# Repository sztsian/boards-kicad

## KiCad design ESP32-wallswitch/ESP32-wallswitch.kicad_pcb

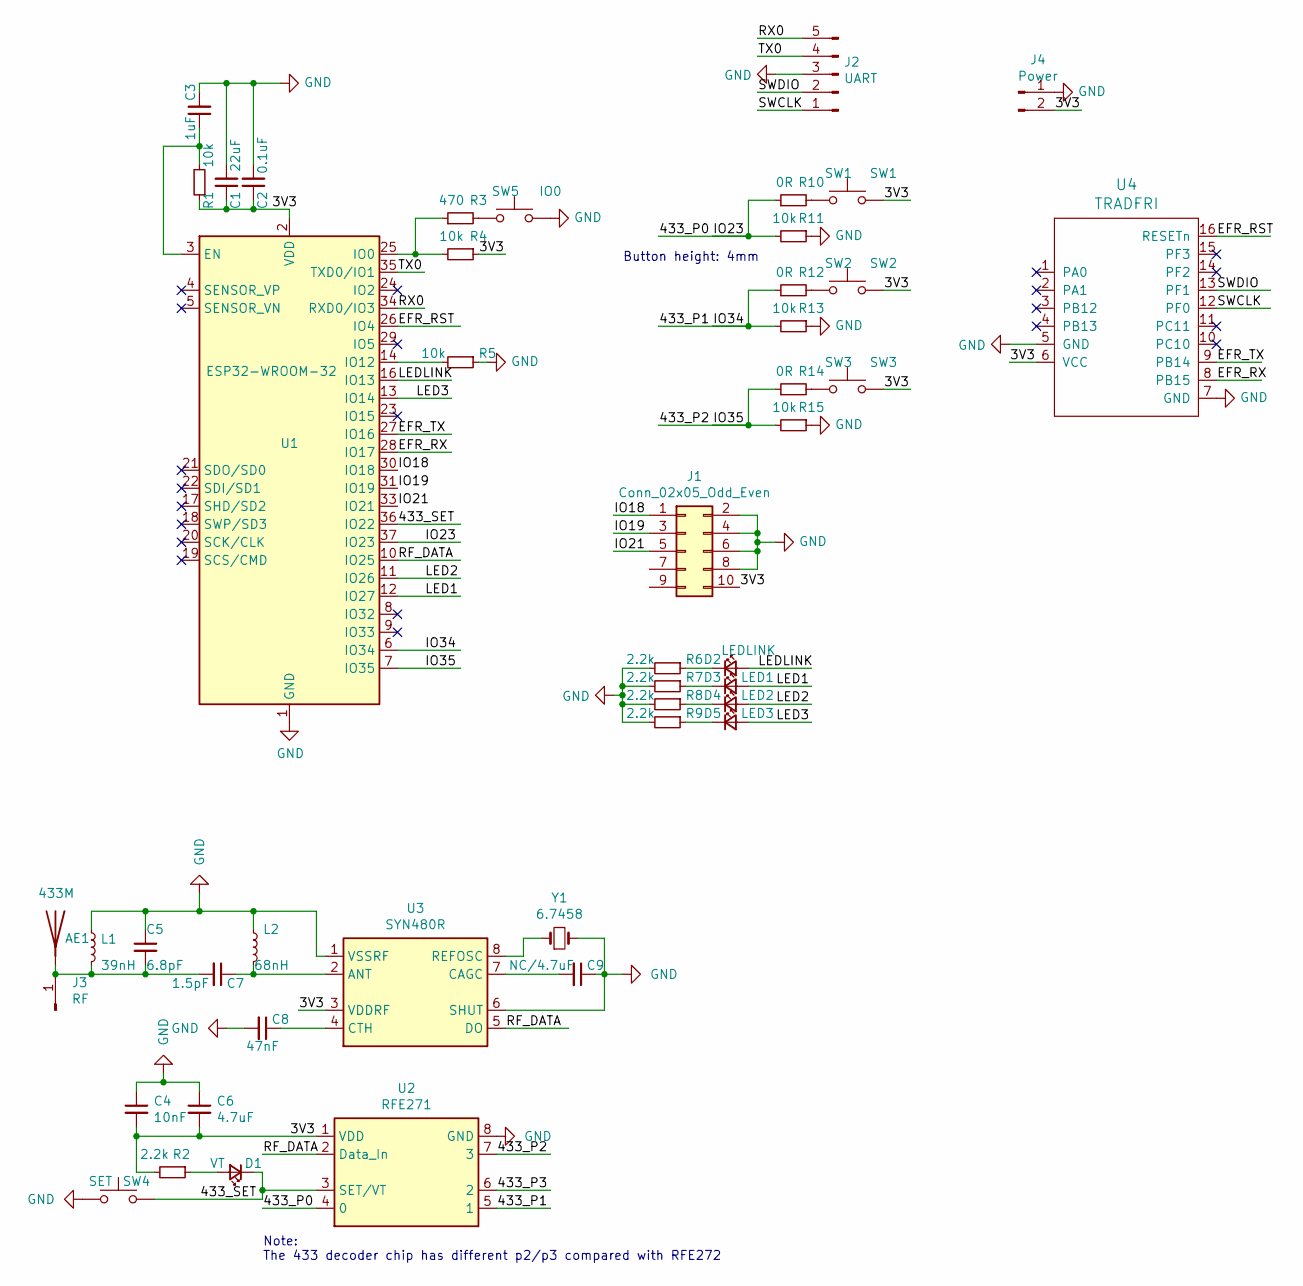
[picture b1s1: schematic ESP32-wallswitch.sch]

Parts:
AE1: 433M; PinHeader_1x01_P2.54mm_Vertical
C1: 22uF; C_0603_1608Metric_Pad1.08x0.95mm_HandSolder
C2: 0.1uF; C_0603_1608Metric_Pad1.08x0.95mm_HandSolder
C3: 1uF; C_0603_1608Metric_Pad1.08x0.95mm_HandSolder
C4: 10nF; C_0402_1005Metric_Pad0.74x0.62mm_HandSolder
C5: 6.8pF; C_0402_1005Metric_Pad0.74x0.62mm_HandSolder
C6: 4.7uF; C_0402_1005Metric_Pad0.74x0.62mm_HandSolder
C7: 1.5pF; C_0402_1005Metric_Pad0.74x0.62mm_HandSolder
C8: 47nF; C_0402_1005Metric_Pad0.74x0.62mm_HandSolder
C9: NC/4.7uF; C_0402_1005Metric_Pad0.74x0.62mm_HandSolder
D1: VT; LED_0603_1608Metric_Pad1.05x0.95mm_HandSolder
D2: LEDLINK; LED_0603_1608Metric_Pad1.05x0.95mm_HandSolder
D3: LED1; LED_0603_1608Metric_Pad1.05x0.95mm_HandSolder
D4: LED2; LED_0603_1608Metric_Pad1.05x0.95mm_HandSolder
D5: LED3; LED_0603_1608Metric_Pad1.05x0.95mm_HandSolder
J1: Conn_02x05_Odd_Even; PinSocket_2x05_P2.00mm_Vertical_SMD
J2: UART; PinHeader_1x05_P2.54mm_Vertical
J3: RF; PinSocket_1x01_P2.00mm_Vertical
J4: Power; PinHeader_1x02_P2.54mm_Vertical
L1: 39nH; L_0402_1005Metric_Pad0.77x0.64mm_HandSolder
L2: 68nH; L_0402_1005Metric_Pad0.77x0.64mm_HandSolder
R1, R4, R5, R11, R13, R15: 10k; R_0603_1608Metric_Pad0.98x0.95mm_HandSolder
R2: 2.2k; R_0402_1005Metric_Pad0.72x0.64mm_HandSolder
R3: 470; R_0603_1608Metric_Pad0.98x0.95mm_HandSolder
R6, R7, R8, R9: 2.2k; R_0603_1608Metric_Pad0.98x0.95mm_HandSolder
R10, R12, R14: 0R; R_0603_1608Metric_Pad0.98x0.95mm_HandSolder
SW1: SW1; SW_Push_1P1T_NO_6x6mm_H9.5mm
SW2: SW2; SW_Push_1P1T_NO_6x6mm_H9.5mm
SW3: SW3; SW_Push_1P1T_NO_6x6mm_H9.5mm
SW4: SET; smd_push
SW5: IO0; smd_push
U1: ESP32-WROOM-32
U2: RFE271; SOP-8_3.76x4.96mm_P1.27mm
U3: SYN480R; SOP-8_3.76x4.96mm_P1.27mm
U4: TRADFRI; TRADFRI_PCB2.0
Y1: 6.7458; Crystal_SMD_HC49-SD

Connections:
/3V3: C1.1, C2.1, C4.2, C6.2, J1.10, J4.2, R1.1, R2.2, R4.1, SW1.2, SW2.2, SW3.2, U1.2 (VDD), U2.1 (VDD), U3.3 (VDDRF), U4.6 (VCC)
/433_P0: R10.1, R11.2, U1.37 (IO23), U2.4 (0)
/433_P1: R12.1, R13.2, U1.6 (IO34), U2.5 (1)
/433_P2: R14.1, R15.2, U1.7 (IO35), U2.7 (3)
/433_SET: D1.1 (K), SW4.2, U1.36 (IO22), U2.3 (SET/VT)
/EFR_RST: U1.26 (IO4), U4.16 (RESETn)
/EFR_RX: U1.28 (IO17), U4.8 (PB15)
/EFR_TX: U1.27 (IO16), U4.9 (PB14)
/IO18: J1.1, U1.30 (IO18)
/IO19: J1.3, U1.31 (IO19)
/IO21: J1.5, U1.33 (IO21)
/LED1: D3.2 (A), U1.12 (IO27)
/LED2: D4.2 (A), U1.11 (IO26)
/LED3: D5.2 (A), U1.13 (IO14)
/LEDLINK: D2.2 (A), U1.16 (IO13)
/RF_DATA: U1.10 (IO25), U2.2 (Data_In), U3.5 (DO)
/RX0: J2.5, U1.34 (RXD0/IO3)
/SWCLK: J2.1, U4.12 (PF0)
/SWDIO: J2.2, U4.13 (PF1)
/TX0: J2.4, U1.35 (TXD0/IO1)
GND: C1.2, C2.2, C3.2, C4.1, C5.1, C6.1, C8.2, C9.1, J1.2, J1.4, J1.6, J1.8, J2.3, J4.1, L1.1, L2.1, R5.1, R6.2, R7.2, R8.2, R9.2, R11.1, R13.1, R15.1, SW4.1, SW5.2, U1.1 (GND), U1.15 (GND), U1.38 (GND), U1.39 (GND), U2.8 (GND), U3.1 (VSSRF), U3.6 (SHUT), U4.5 (GND), U4.7 (GND), Y1.2
unnamed: AE1.1, C5.2, C7.2, J3.1, L1.2
unnamed: C3.1, R1.2, U1.3 (EN)
unnamed: C7.1, L2.2, U3.2 (ANT)
unnamed: C8.1, U3.4 (CTH)
unnamed: C9.2, U3.7 (CAGC)
unnamed: D1.2 (A), R2.1
unnamed: D2.1 (K), R6.1
unnamed: D3.1 (K), R7.1
unnamed: D4.1 (K), R8.1
unnamed: D5.1 (K), R9.1
unnamed: R3.1, R4.2, U1.25 (IO0)
unnamed: R3.2, SW5.1
unnamed: R5.2, U1.14 (IO12)
unnamed: R10.2, SW1.1
unnamed: R12.2, SW2.1
unnamed: R14.2, SW3.1
unnamed: U3.8 (REFOSC), Y1.1

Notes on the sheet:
Note: The 433 decoder chip has different p2/p3 compared with RFE272
Button height: 4mm

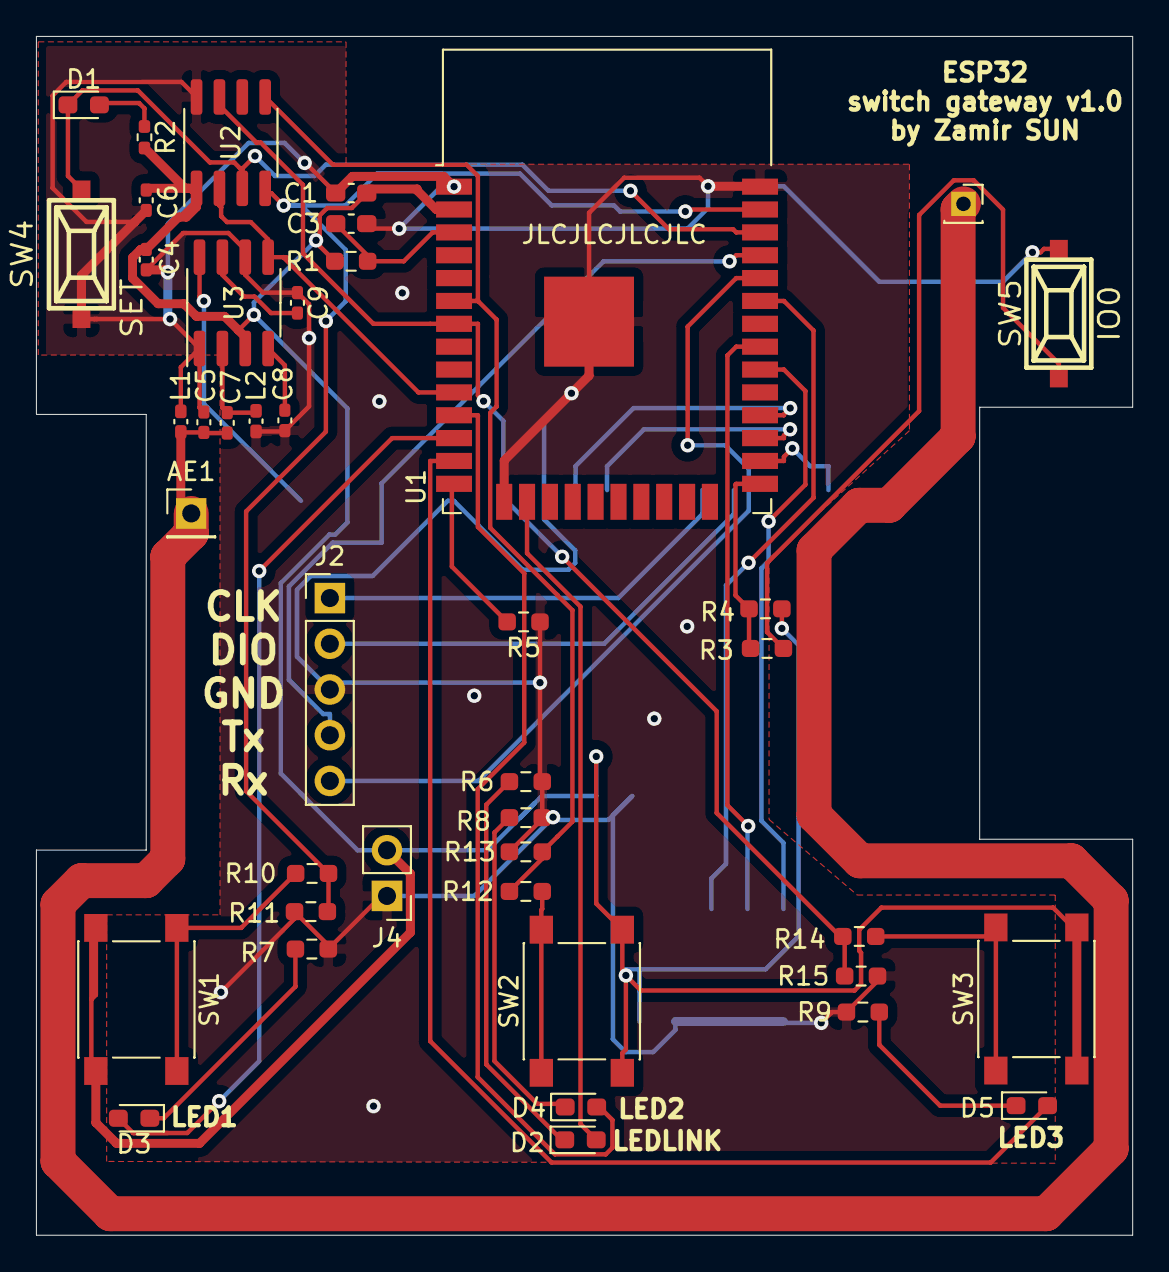
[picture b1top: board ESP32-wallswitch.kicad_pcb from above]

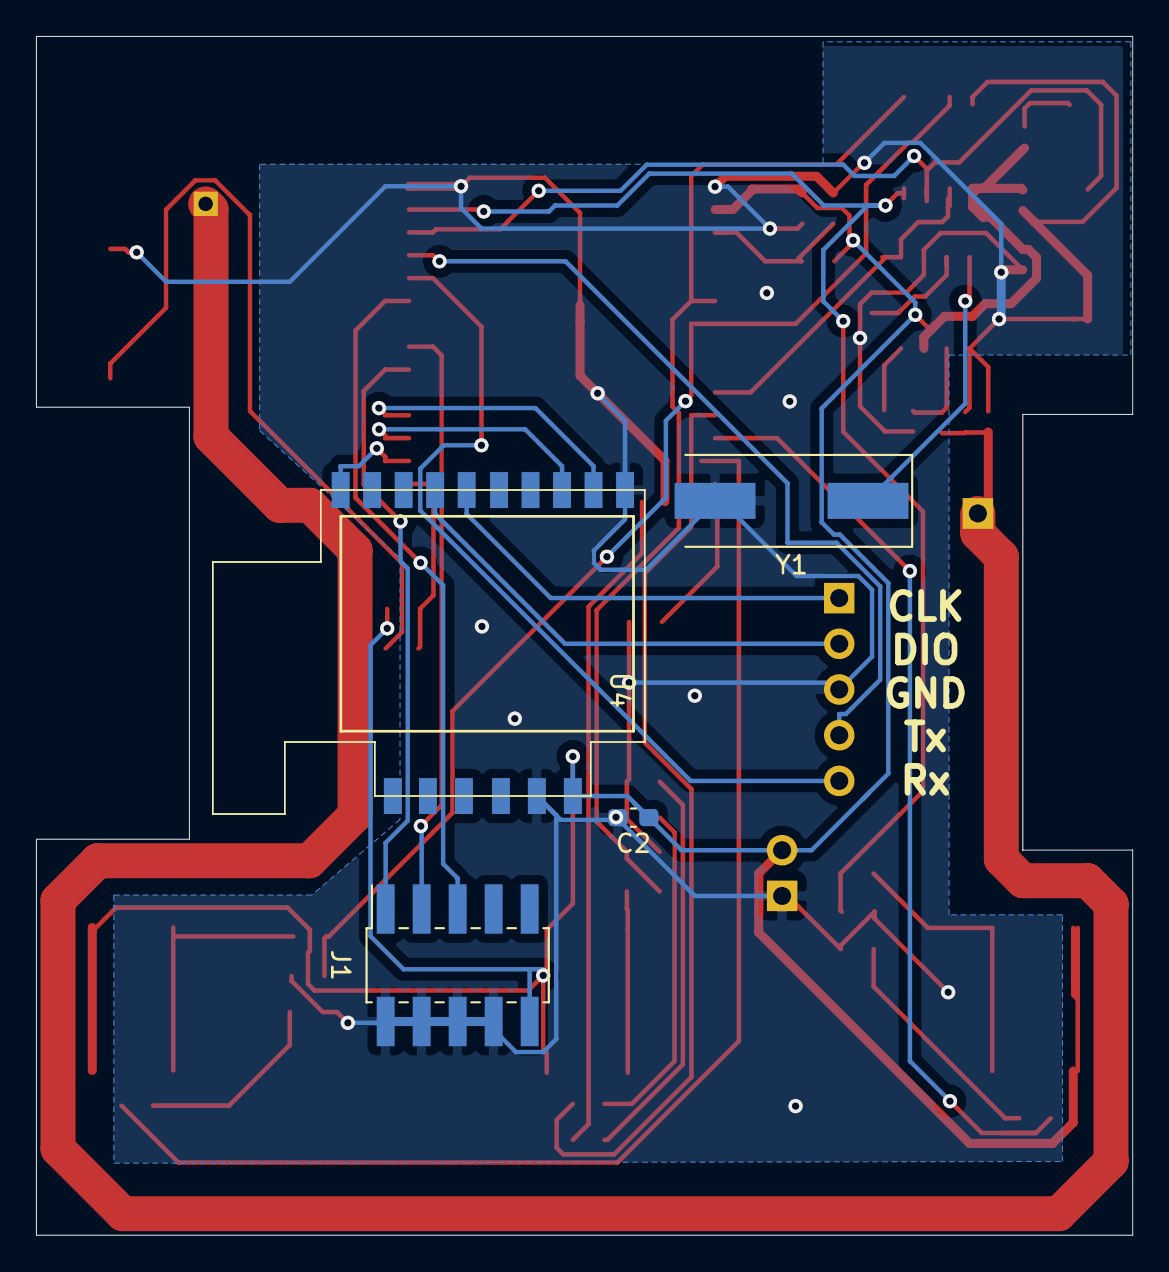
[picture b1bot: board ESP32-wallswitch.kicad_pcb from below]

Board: 2 copper layers, 60.9 x 66.6 mm, 46 parts (4 on the bottom side), 38 nets.

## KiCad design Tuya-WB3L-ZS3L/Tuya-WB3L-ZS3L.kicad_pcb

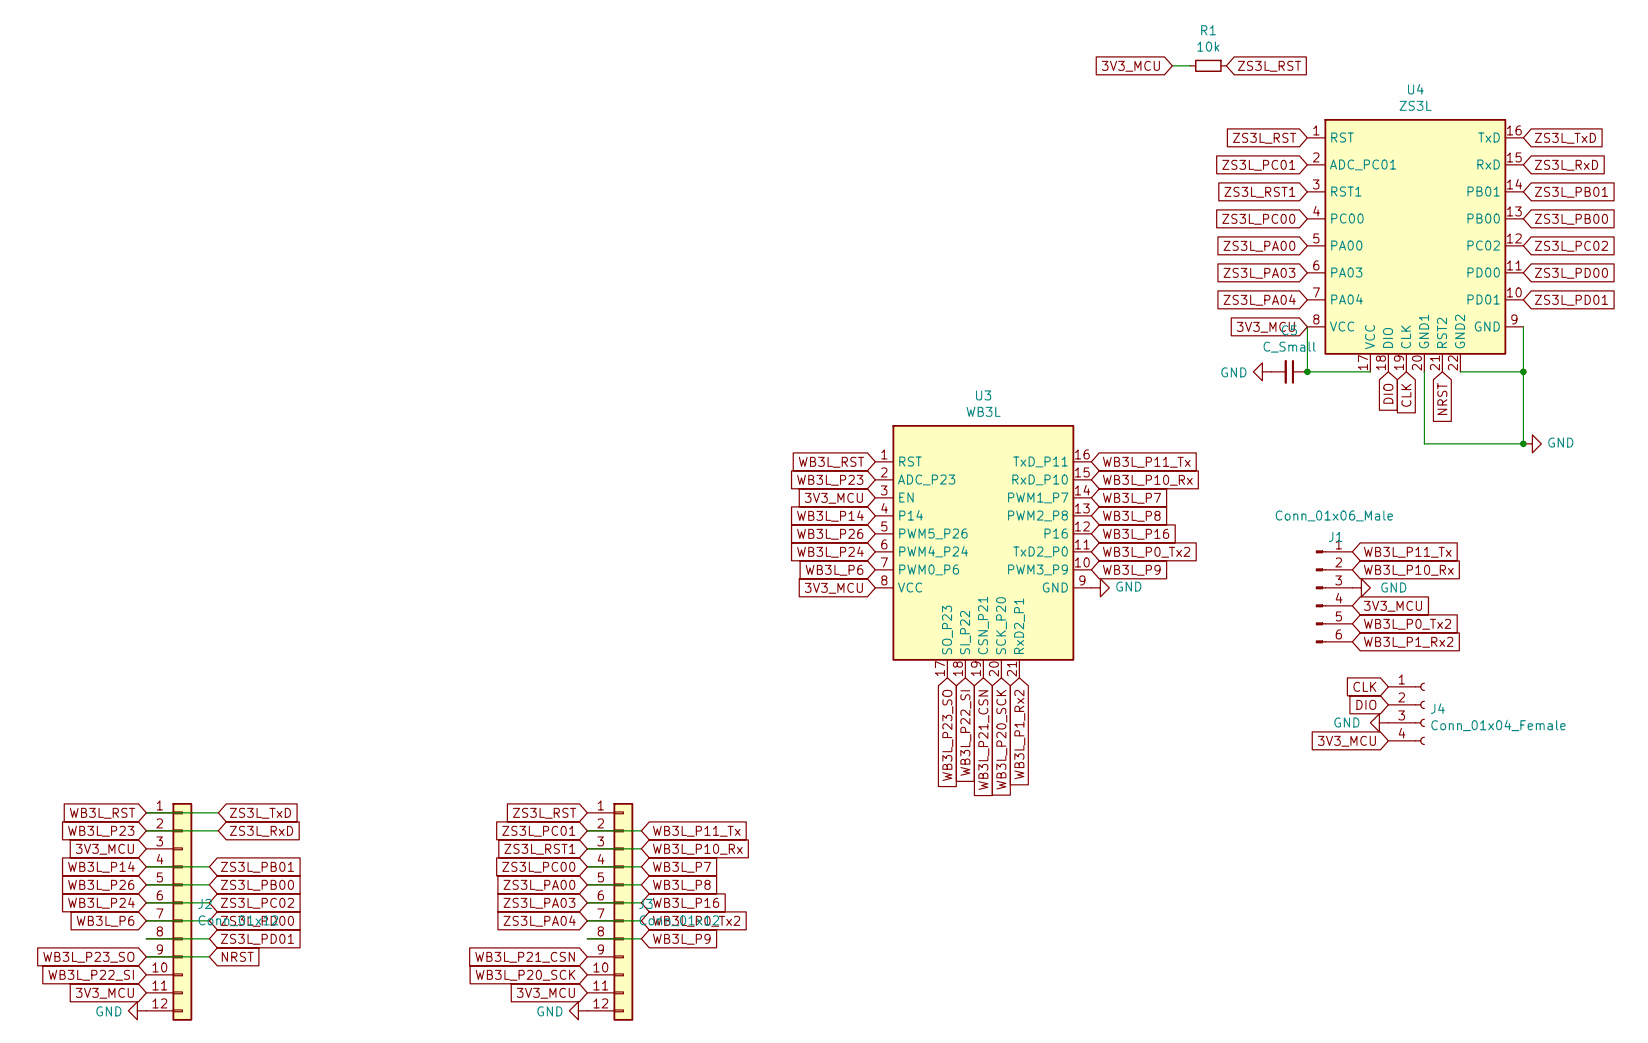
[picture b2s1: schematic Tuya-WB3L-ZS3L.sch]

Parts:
C5: C_Small; C_0603_1608Metric_Pad1.08x0.95mm_HandSolder
J1: Conn_01x06_Male; PinHeader_1x06_P2.54mm_Vertical
J2, J3: Conn_01x12; PinHeader_1x12_P2.54mm_Vertical
J4: Conn_01x04_Female; PinHeader_1x04_P2.54mm_Vertical
R1: 10k; R_0603_1608Metric_Pad0.98x0.95mm_HandSolder
U3: WB3L
U4: ZS3L

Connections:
3V3_MCU: C5.1, J1.4, J2.3, J2.11, J3.11, J4.4, R1.2, U3.3 (EN), U3.8 (VCC), U4.8 (VCC), U4.17 (VCC)
CLK: J4.1, U4.19 (CLK)
DIO: J4.2, U4.18 (DIO)
GND: C5.2, J1.3, J2.12, J3.12, J4.3, U3.9 (GND), U4.9 (GND), U4.20 (GND1), U4.22 (GND2)
NRST: J2.9, U3.17 (SO_P23), U4.21 (RST2)
WB3L_P0_Tx2: J1.5, J3.7, U3.11 (TxD2_P0), U4.7 (PA04)
WB3L_P1_Rx2: J1.6, U3.21 (RxD2_P1)
WB3L_P6: J2.7, U3.7 (PWM0_P6), U4.11 (PD00)
WB3L_P7: J3.4, U3.14 (PWM1_P7), U4.4 (PC00)
WB3L_P8: J3.5, U3.13 (PWM2_P8), U4.5 (PA00)
WB3L_P9: J3.8, U3.10 (PWM3_P9)
WB3L_P10_Rx: J1.2, J3.3, U3.15 (RxD_P10), U4.3 (RST1)
WB3L_P11_Tx: J1.1, J3.2, U3.16 (TxD_P11), U4.2 (ADC_PC01)
WB3L_P14: J2.4, U3.4 (P14), U4.14 (PB01)
WB3L_P16: J3.6, U3.12 (P16), U4.6 (PA03)
WB3L_P20_SCK: J3.10, U3.20 (SCK_P20)
WB3L_P21_CSN: J3.9, U3.19 (CSN_P21)
WB3L_P22_SI: J2.10, U3.18 (SI_P22)
WB3L_P23: J2.2, U3.2 (ADC_P23), U4.15 (RxD)
WB3L_P24: J2.6, U3.6 (PWM4_P24), U4.12 (PC02)
WB3L_P26: J2.5, U3.5 (PWM5_P26), U4.13 (PB00)
WB3L_RST: J2.1, U3.1 (RST), U4.16 (TxD)
ZS3L_PD01: J2.8, U4.10 (PD01)
ZS3L_RST: J3.1, R1.1, U4.1 (RST)

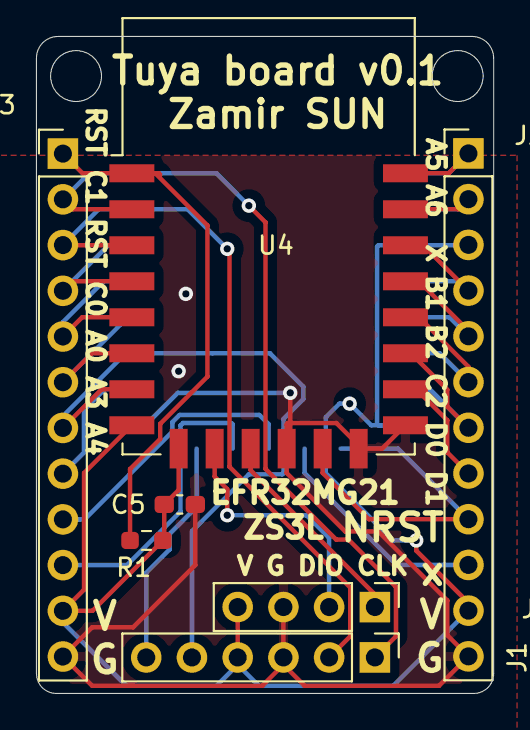
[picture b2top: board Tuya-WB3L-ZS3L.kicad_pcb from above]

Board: 2 copper layers, 25.4 x 36.5 mm, 8 parts (1 on the bottom side), 24 nets.

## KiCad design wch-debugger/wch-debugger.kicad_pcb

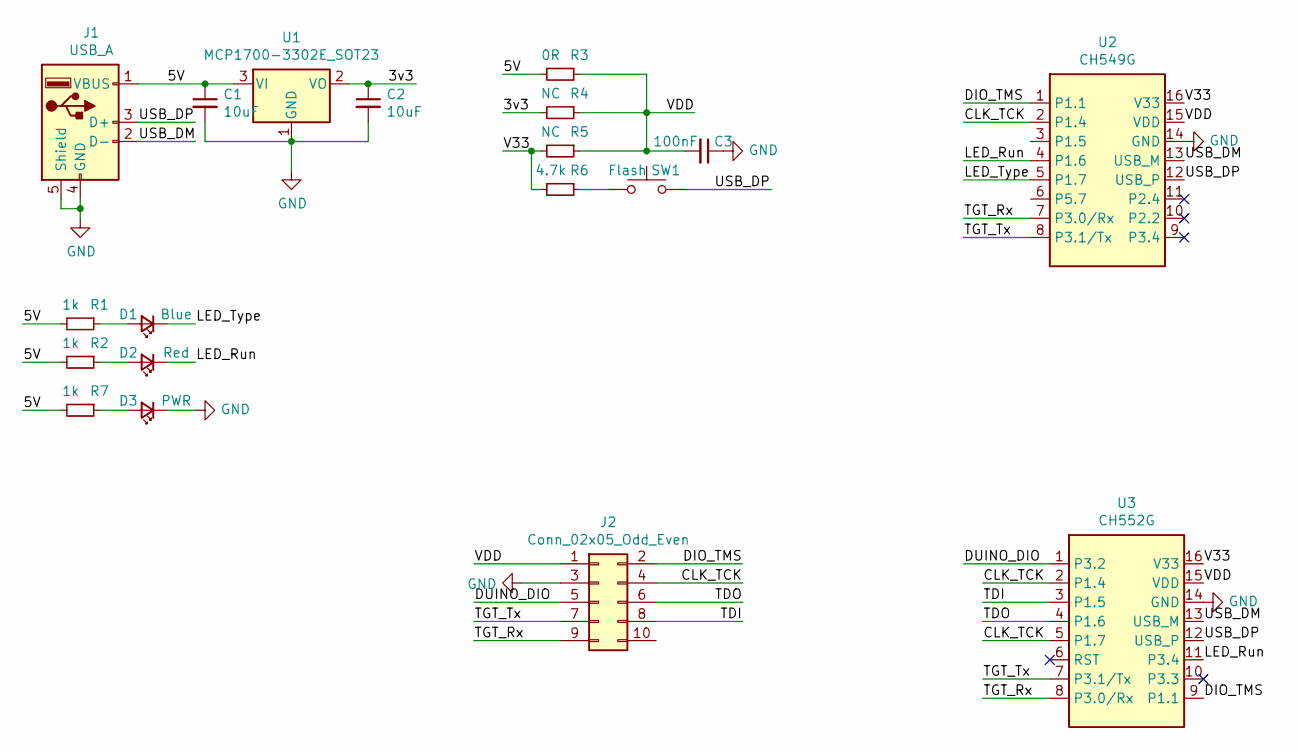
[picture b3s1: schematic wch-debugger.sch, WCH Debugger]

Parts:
C1, C2: 10uF; C_0603_1608Metric_Pad1.08x0.95mm_HandSolder
C3: 100nF; C_0603_1608Metric_Pad1.08x0.95mm_HandSolder
D1: Blue; LED_0603_1608Metric_Pad1.05x0.95mm_HandSolder
D2: Red; LED_0603_1608Metric_Pad1.05x0.95mm_HandSolder
D3: PWR; LED_0603_1608Metric_Pad1.05x0.95mm_HandSolder
J1: USB_A; USB_A_Plug
J2: Conn_02x05_Odd_Even; PinHeader_2x05_P2.54mm_Vertical
R1, R2, R7: 1k; R_0603_1608Metric_Pad0.98x0.95mm_HandSolder
R3: 0R; R_0603_1608Metric_Pad0.98x0.95mm_HandSolder
R4, R5: NC; R_0603_1608Metric_Pad0.98x0.95mm_HandSolder
R6: 4.7k; R_0603_1608Metric_Pad0.98x0.95mm_HandSolder
SW1: Flash; smd_push
U1: MCP1700-3302E_SOT23; SOT-23
U2: CH549G; SOIC-16_3.9x9.9mm_P1.27mm
U3: CH552G; SOIC-16_3.9x9.9mm_P1.27mm

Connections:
/3v3: C2.1, R4.2, U1.2 (VO)
/5V: C1.1, J1.1 (VBUS), R1.2, R2.2, R3.2, R7.2, U1.3 (VI)
/CLK_TCK: J2.4, U2.2 (P1.4), U3.2 (P1.4), U3.5 (P1.7)
/DIO_TMS: J2.2, U2.1 (P1.1), U3.9 (P1.1)
/DUINO_DIO: J2.5, U3.1 (P3.2)
/LED_Run: D2.1 (K), U2.4 (P1.6), U3.11 (P3.4)
/LED_Type: D1.1 (K), U2.5 (P1.7)
/TDI: J2.8, U3.3 (P1.5)
/TDO: J2.6, U3.4 (P1.6)
/TGT_Rx: J2.9, U2.7 (P3.0/Rx), U3.8 (P3.0/Rx)
/TGT_Tx: J2.7, U2.8 (P3.1/Tx), U3.7 (P3.1/Tx)
/USB_DM: J1.2 (D-), U2.13 (USB_M), U3.13 (USB_M)
/USB_DP: J1.3 (D+), SW1.2, U2.12 (USB_P), U3.12 (USB_P)
/V33: R5.2, R6.2, U2.16 (V33), U3.16 (V33)
/VDD: C3.2, J2.1, R3.1, R4.1, R5.1, U2.15 (VDD), U3.15 (VDD)
GND: C1.2, C2.2, C3.1, D3.1 (K), J1.4 (GND), J1.5 (Shield), J2.3, U1.1 (GND), U2.14 (GND), U3.14 (GND)
unnamed: D1.2 (A), R1.1
unnamed: D2.2 (A), R2.1
unnamed: D3.2 (A), R7.1
unnamed: R6.1, SW1.1

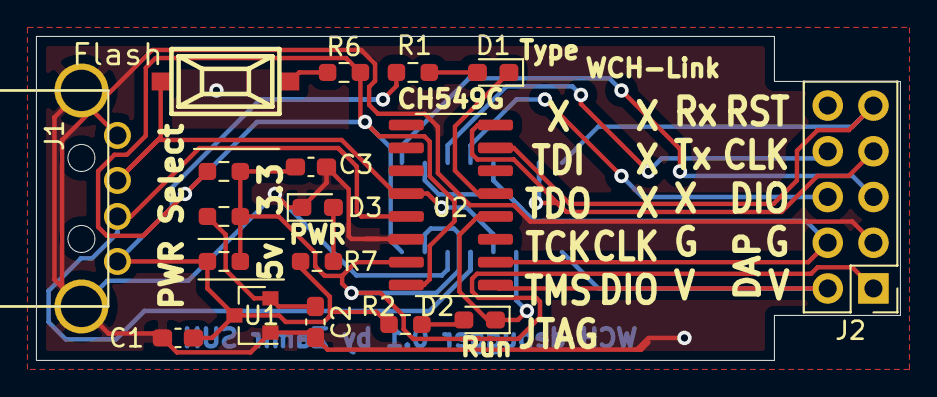
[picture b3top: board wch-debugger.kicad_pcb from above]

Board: 2 copper layers, 48.0 x 18.0 mm, 19 parts (1 on the bottom side), 20 nets.

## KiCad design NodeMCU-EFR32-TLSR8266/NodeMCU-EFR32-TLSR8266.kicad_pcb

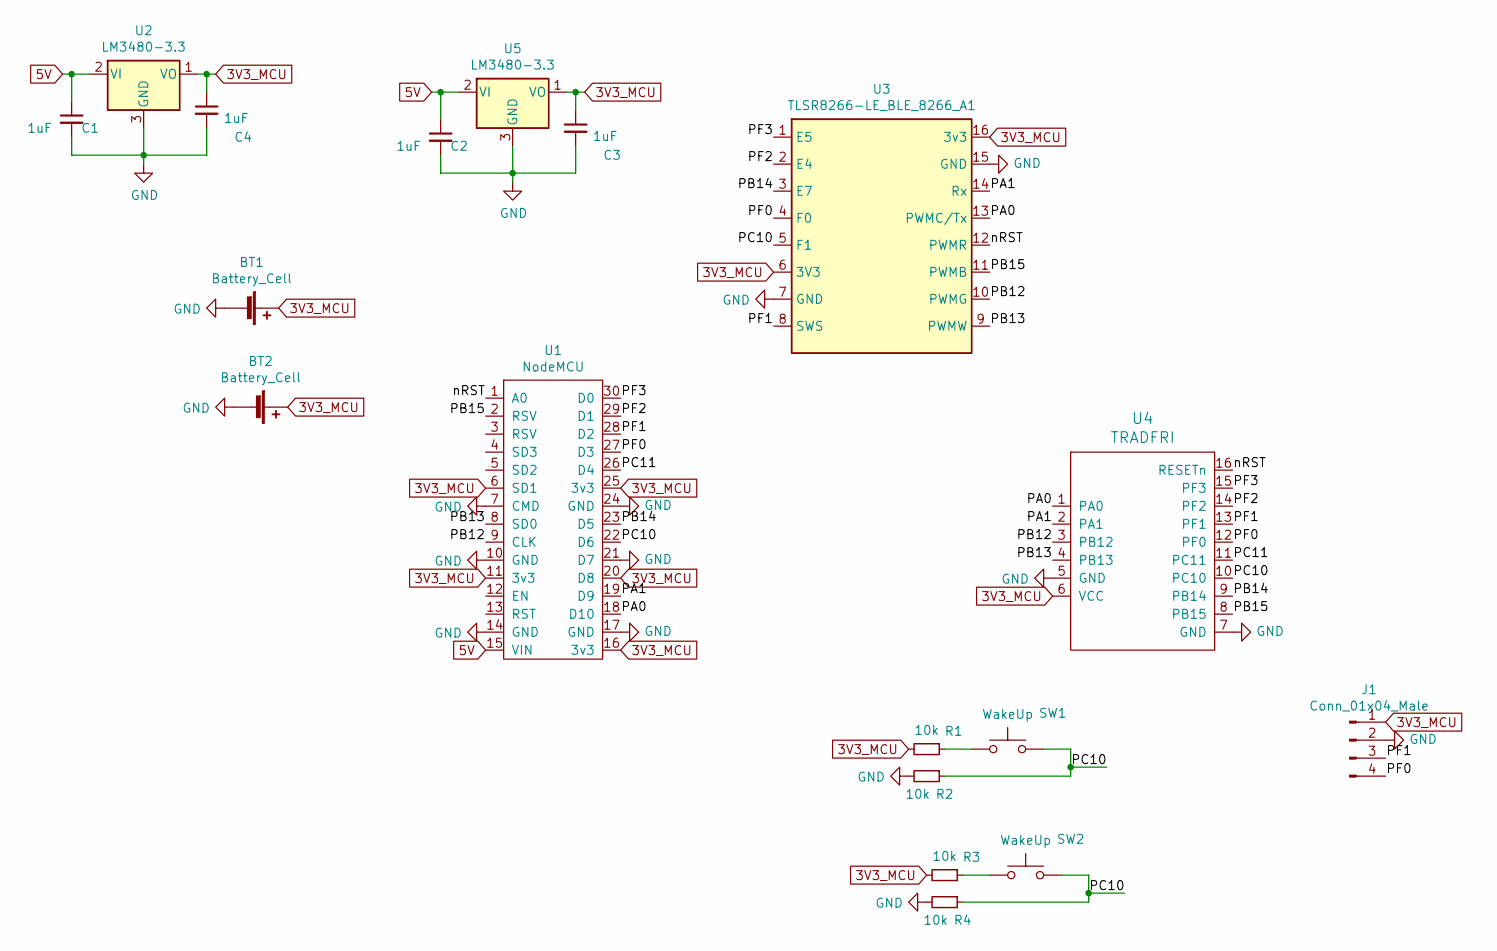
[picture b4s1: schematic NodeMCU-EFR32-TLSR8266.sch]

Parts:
BT1, BT2: Battery_Cell; BatteryHolder_Keystone_1060_1x2032
C1, C2: 1uF; C_0603_1608Metric
C3, C4: 1uF; C_0603_1608Metric_Pad1.08x0.95mm_HandSolder
J1: Conn_01x04_Male; PinHeader_1x04_P2.54mm_Vertical
R1, R2, R3, R4: 10k; R_0603_1608Metric_Pad0.98x0.95mm_HandSolder
SW1, SW2: WakeUp; smd_push
U1: NodeMCU
U2, U5: LM3480-3.3; SOT-23
U3: TLSR8266-LE_BLE_8266_A1; ESP-12E-16pin
U4: TRADFRI; TRADFRI_PCB2.0

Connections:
3V3_MCU: BT1.1 (+), BT2.1 (+), C3.1, C4.1, J1.1, R1.2, R3.2, U1.6 (SD1), U1.11 (3v3), U1.16 (3v3), U1.20 (D8), U1.25 (3v3), U2.1 (VO), U3.6 (3V3), U3.16 (3v3), U4.6 (VCC), U5.1 (VO)
5V: C1.1, C2.1, U1.15 (VIN), U2.2 (VI), U5.2 (VI)
/PA0: U1.18 (D10), U3.13 (PWMC/Tx), U4.1 (PA0)
/PA1: U1.19 (D9), U3.14 (Rx), U4.2 (PA1)
/PB12: U1.9 (CLK), U3.10 (PWMG), U4.3 (PB12)
/PB13: U1.8 (SD0), U3.9 (PWMW), U4.4 (PB13)
/PB14: U1.23 (D5), U3.3 (E7), U4.9 (PB14)
/PB15: U1.2 (RSV), U3.11 (PWMB), U4.8 (PB15)
/PC10: R2.1, R4.1, SW1.2, SW2.2, U1.22 (D6), U3.5 (F1), U4.10 (PC10)
/PC11: U1.26 (D4), U4.11 (PC11)
/PF0: J1.4, U1.27 (D3), U3.4 (F0), U4.12 (PF0)
/PF1: J1.3, U1.28 (D2), U3.8 (SWS), U4.13 (PF1)
/PF2: U1.29 (D1), U3.2 (E4), U4.14 (PF2)
/PF3: U1.30 (D0), U3.1 (E5), U4.15 (PF3)
/nRST: U1.1 (A0), U3.12 (PWMR), U4.16 (RESETn)
GND: BT1.2 (-), BT2.2 (-), C1.2, C2.2, C3.2, C4.2, J1.2, R2.2, R4.2, U1.7 (CMD), U1.10 (GND), U1.14 (GND), U1.17 (GND), U1.21 (D7), U1.24 (GND), U2.3 (GND), U3.7 (GND), U3.15 (GND), U4.5 (GND), U4.7 (GND), U5.3 (GND)
unnamed: R1.1, SW1.1
unnamed: R3.1, SW2.1

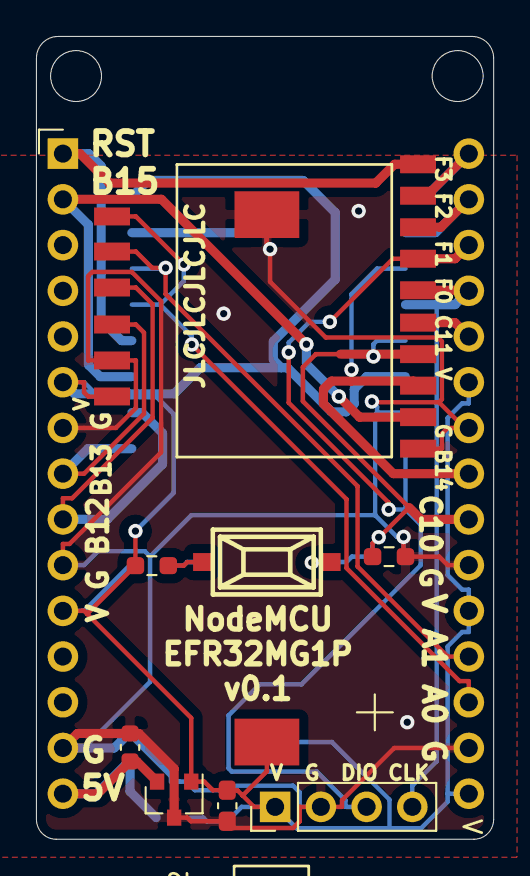
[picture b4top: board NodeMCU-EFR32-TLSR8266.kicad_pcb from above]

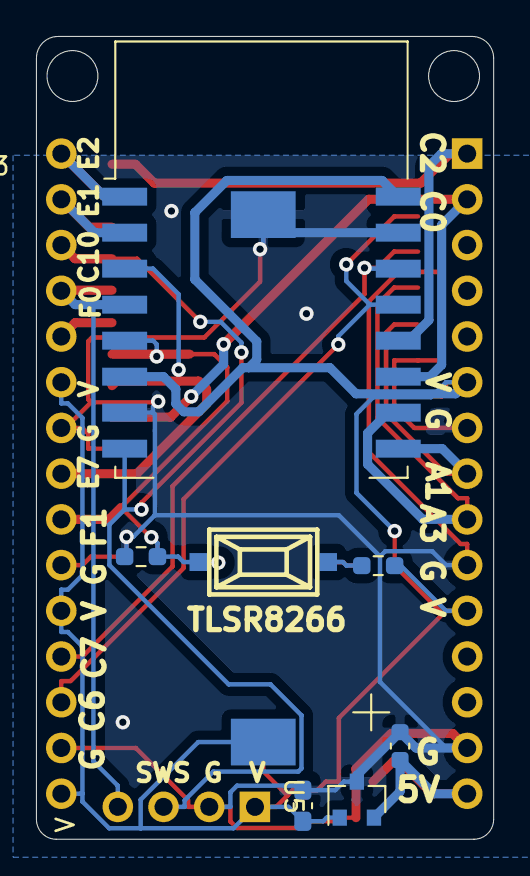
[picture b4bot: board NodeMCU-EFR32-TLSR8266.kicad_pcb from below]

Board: 2 copper layers, 25.4 x 44.6 mm, 18 parts (8 on the bottom side), 18 nets.

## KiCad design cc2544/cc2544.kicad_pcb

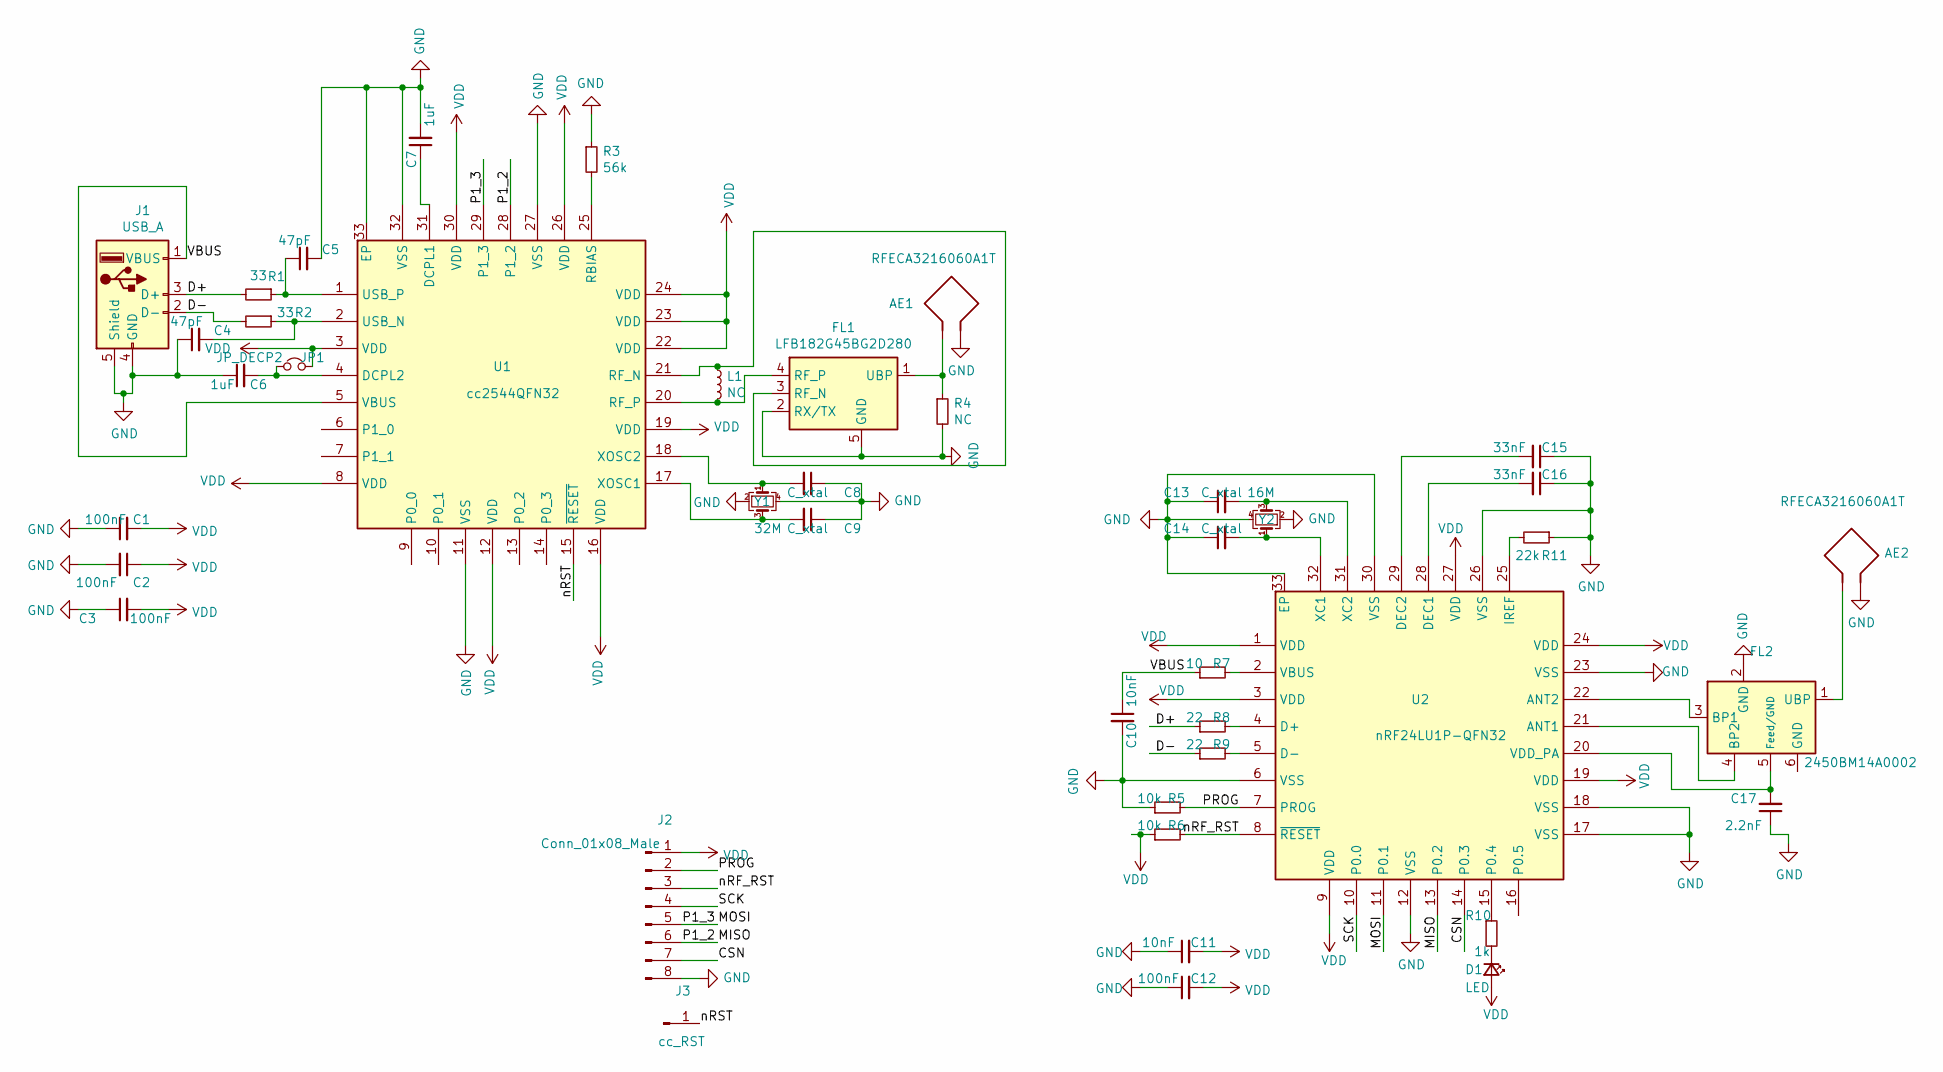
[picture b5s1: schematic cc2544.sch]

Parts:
AE1, AE2: RFECA3216060A1T; Johanson_2450AT18x100
C1, C2, C3, C12: 100nF; C_0603_1608Metric
C4, C5: 47pF; C_0603_1608Metric
C6, C7: 1uF; C_0603_1608Metric
C8, C9, C13, C14: C_xtal; C_0603_1608Metric
C10, C11: 10nF; C_0603_1608Metric
C15, C16: 33nF; C_0603_1608Metric
C17: 2.2nF; C_0603_1608Metric
D1: LED; LED_0603_1608Metric
FL1: LFB182G45BG2D280; Balun_Johanson_1.6x0.8mm
FL2: 2450BM14A0002; Balun_Johanson_1.6x0.8mm
J1: USB_A; USB_A_Plug
J2: Conn_01x08_Male; PinHeader_1x08_P2.54mm_Vertical
J3: cc_RST; PinHeader_1x01_P2.54mm_Vertical
JP1: JP_DECP2; SolderJumper-2_P1.3mm_Bridged_RoundedPad1.0x1.5mm
L1: NC; L_0603_1608Metric
R1, R2: 33; R_0603_1608Metric
R3: 56k; R_0603_1608Metric
R4: NC; R_0603_1608Metric
R5, R6: 10k; R_0603_1608Metric
R7: 10; R_0603_1608Metric
R8, R9: 22; R_0603_1608Metric
R10: 1k; R_0603_1608Metric
R11: 22k; R_0603_1608Metric
U1: cc2544QFN32; QFN-32-1EP_5x5mm_P0.5mm_EP3.45x3.45mm
U2: nRF24LU1P-QFN32; QFN-32-1EP_5x5mm_P0.5mm_EP3.45x3.45mm
Y1: 32M; Crystal_SMD_3225-4Pin_3.2x2.5mm
Y2: 16M; Crystal_SMD_2520-4Pin_2.5x2.0mm

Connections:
/CSN: J2.7, U2.14 (P0.3)
/D+: J1.3 (D+), R1.2, R8.1
/D-: J1.2 (D-), R2.2, R9.1
/MISO: J2.6, U1.28 (P1_2), U2.13 (P0.2)
/MOSI: J2.5, U1.29 (P1_3), U2.11 (P0.1)
/PROG: J2.2, R5.2, U2.7 (PROG)
/SCK: J2.4, U2.10 (P0.0)
/VBUS: C10.1, J1.1 (VBUS), R7.1, U1.5 (VBUS)
/nRF_RST: J2.3, R6.2, U2.8 (~RESET)
/nRST: J3.1, U1.15 (~RESET)
GND: AE1.2, AE2.2, C1.1, C2.2, C3.1, C4.1, C5.2, C6.1, C7.2, C8.1, C9.1, C10.2, C11.1, C12.1, C13.1, C14.1, C15.1, C16.1, C17.1, FL1.2 (RX/TX), FL1.5 (GND), FL1.6 (GND), FL2.2 (GND), J1.4 (GND), J1.5 (Shield), J2.8, R3.1, R4.2, R5.1, R11.1, U1.11 (VSS), U1.27 (VSS), U1.32 (VSS), U1.33 (EP), U2.6 (VSS), U2.12 (VSS), U2.17 (VSS), U2.18 (VSS), U2.23 (VSS), U2.26 (VSS), U2.30 (VSS), U2.33 (EP), Y1.2, Y1.4, Y2.2, Y2.4
unnamed: AE1.1, FL1.1 (UBP), R4.1
unnamed: AE2.1, FL2.1 (UBP)
unnamed: C4.2, R2.1, U1.2 (USB_N)
unnamed: C5.1, R1.1, U1.1 (USB_P)
unnamed: C6.2, JP1.1, U1.4 (DCPL2)
unnamed: C7.1, U1.31 (DCPL1)
unnamed: C8.2, U1.18 (XOSC2), Y1.1
unnamed: C9.2, U1.17 (XOSC1), Y1.3
unnamed: C13.2, U2.31 (XC2), Y2.3
unnamed: C14.2, U2.32 (XC1), Y2.1
unnamed: C15.2, U2.29 (DEC2)
unnamed: C16.2, U2.28 (DEC1)
unnamed: C17.2, FL2.5 (Feed/GND), U2.20 (VDD_PA)
unnamed: D1.1 (K), R10.2
unnamed: FL1.3 (RF_N), L1.1, U1.21 (RF_N)
unnamed: FL1.4 (RF_P), L1.2, U1.20 (RF_P)
unnamed: FL2.3 (BP1), U2.22 (ANT2)
unnamed: FL2.4 (BP2), U2.21 (ANT1)
unnamed: R3.2, U1.25 (RBIAS)
unnamed: R7.2, U2.2 (VBUS)
unnamed: R8.2, U2.4 (D+)
unnamed: R9.2, U2.5 (D-)
unnamed: R10.1, U2.15 (P0.4)
unnamed: R11.2, U2.25 (IREF)
VDD: C1.2, C2.1, C3.2, C11.2, C12.2, D1.2 (A), J2.1, JP1.2, R6.1, U1.3 (VDD), U1.8 (VDD), U1.12 (VDD), U1.16 (VDD), U1.19 (VDD), U1.22 (VDD), U1.23 (VDD), U1.24 (VDD), U1.26 (VDD), U1.30 (VDD), U2.1 (VDD), U2.3 (VDD), U2.9 (VDD), U2.19 (VDD), U2.24 (VDD), U2.27 (VDD)

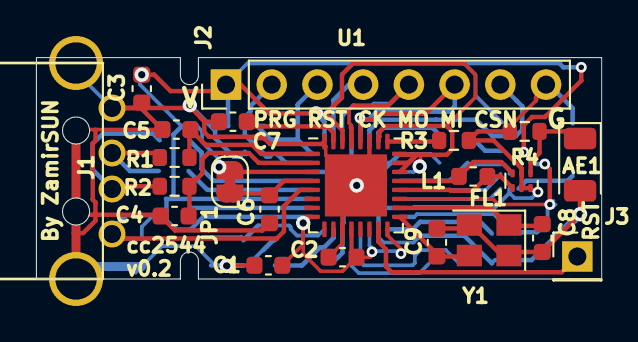
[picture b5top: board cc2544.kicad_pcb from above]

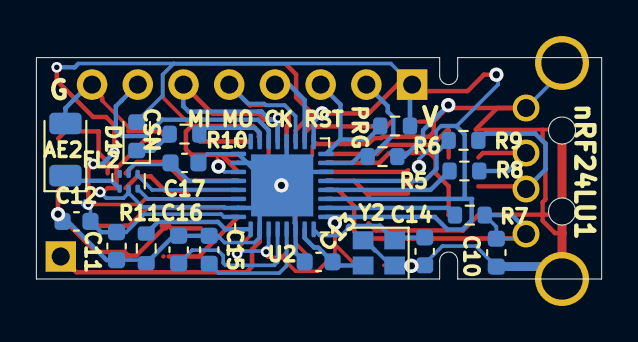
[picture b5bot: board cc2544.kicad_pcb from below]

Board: 2 copper layers, 31.4 x 12.3 mm, 42 parts (20 on the bottom side), 36 nets.
